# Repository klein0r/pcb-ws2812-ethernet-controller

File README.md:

# WS2812 / SK6812 Ethernet Controller Custom PCB

Control your addressable LED with custom software like [WLED](https://github.com/Aircoookie/WLED)

[Gerber-Files](https://github.com/klein0r/pcb-ws2812-ethernet-controller/releases)

## Important notes

The [WT32-ETH01](https://en.wireless-tag.com/product-item-2.html) has been released in different revisions. This adapter has been tested with revision 1.2 (length of the WT32-ETH01 PCB is ~5.5 cm).

**Some revisions may not fit!** I've received a photo of revision 1.4 with a PCB length of ~6.0 cm. Use PCB version 2.0 (or later) of this project to ensure the adapter will fit.

## Preview

## Components

- U1: WT32-ETH01 ESP32
- U2: SN74AHCT125DR
- C1: Capacitor Radial 3.8mm 1000μF 6.3V
- F1: Stelvio Kontek STV PTF/75 + Fuse 5x20mm, 5A (max. 6A)
- J1: Barrel Jack Connector - Wuerth 6941xx301002
- J2: PHC 1725669 - MPT 0,5 / 3-2,54
- J3: PHC 1725669 - MPT 0,5 / 3-2,54
- J4: 1x4 2.54mm Male Pin Headers (for flashing - soldering not required)
- J5: 1x2 2.54mm Male Pin Headers (for flashing - soldering not required / jumper)
- R1: Resistor 0805 330
- R2: Resistor 0805 330

[Component list (Affiliate-Link)](https://haus-auto.com/p/rei/ListeWS2812Eth)

## GPIO

- GPIO2 = Data line 1 of addressable strip
- GPIO4 = Data line 2 of addressable strip

## License

The MIT License (MIT)

Copyright (c) 2026 Matthias Kleine <info@haus-automatisierung.com>

Permission is hereby granted, free of charge, to any person obtaining a copy
of this software and associated documentation files (the "Software"), to deal
in the Software without restriction, including without limitation the rights
to use, copy, modify, merge, publish, distribute, sublicense, and/or sell
copies of the Software, and to permit persons to whom the Software is
furnished to do so, subject to the following conditions:

The above copyright notice and this permission notice shall be included in
all copies or substantial portions of the Software.

THE SOFTWARE IS PROVIDED "AS IS", WITHOUT WARRANTY OF ANY KIND, EXPRESS OR
IMPLIED, INCLUDING BUT NOT LIMITED TO THE WARRANTIES OF MERCHANTABILITY,
FITNESS FOR A PARTICULAR PURPOSE AND NONINFRINGEMENT. IN NO EVENT SHALL THE
AUTHORS OR COPYRIGHT HOLDERS BE LIABLE FOR ANY CLAIM, DAMAGES OR OTHER
LIABILITY, WHETHER IN AN ACTION OF CONTRACT, TORT OR OTHERWISE, ARISING FROM,
OUT OF OR IN CONNECTION WITH THE SOFTWARE OR THE USE OR OTHER DEALINGS IN
THE SOFTWARE.

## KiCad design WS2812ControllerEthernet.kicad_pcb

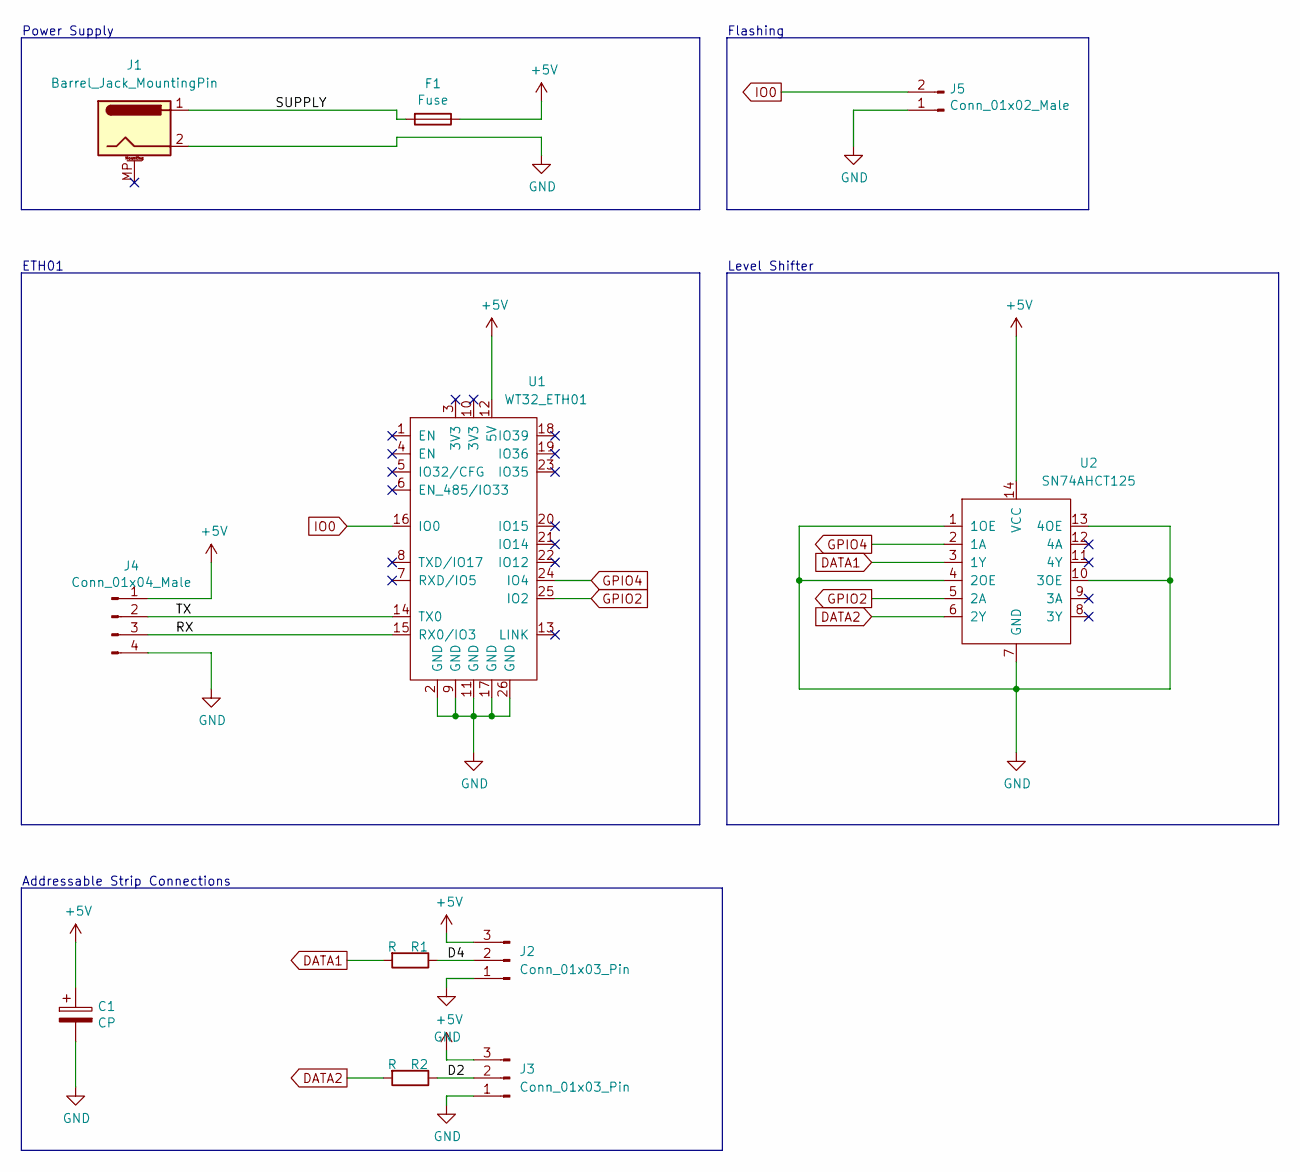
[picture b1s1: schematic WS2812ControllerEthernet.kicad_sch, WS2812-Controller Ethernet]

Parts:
C1: CP; CP_Radial_D8.0mm_P3.80mm
F1: Fuse; Fuse-PTF75_Stelvio
J1: Barrel_Jack_MountingPin; BarrelJack_Wuerth_6941xx301002
J2, J3: Conn_01x03_Pin; TerminalBlock_Phoenix_MPT-0,5-3-2.54_1x03_P2.54mm_Horizontal
J4: Conn_01x04_Male; PinHeader_1x04_P2.54mm_Vertical
J5: Conn_01x02_Male; PinHeader_1x02_P2.54mm_Vertical
R1, R2: R; R_0805_2012Metric_Pad1.20x1.40mm_HandSolder
U1: WT32_ETH01; WT32_ETH01_long
U2: SN74AHCT125; SN74AHCT125D

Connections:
+5V: C1.1, F1.1, J2.3, J3.3, J4.1, U1.12 (5V), U2.14 (VCC)
/D2: J3.2, R2.1
/D4: J2.2, R1.1
/RX: J4.3, U1.15 (RX0/IO3)
/SUPPLY: F1.2, J1.1
/TX: J4.2, U1.14 (TX0)
DATA1: R1.2, U2.3 (1Y)
DATA2: R2.2, U2.6 (2Y)
GND: C1.2, J1.2, J2.1, J3.1, J4.4, J5.1, U1.2 (GND), U1.9 (GND), U1.11 (GND), U1.17 (GND), U1.26 (GND), U2.1 (1OE), U2.4 (2OE), U2.7 (GND), U2.10 (3OE), U2.13 (4OE)
GPIO2: U1.25 (IO2), U2.5 (2A)
GPIO4: U1.24 (IO4), U2.2 (1A)
IO0: J5.2, U1.16 (IO0)

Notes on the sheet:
Addressable Strip Connections
Power Supply
ETH01
Flashing
Level Shifter

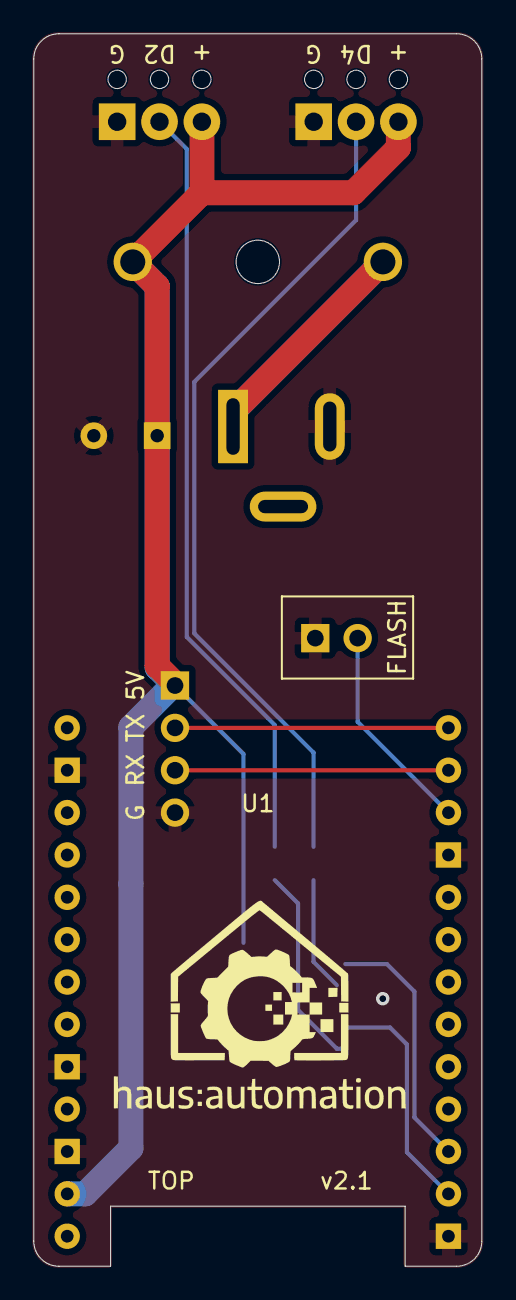
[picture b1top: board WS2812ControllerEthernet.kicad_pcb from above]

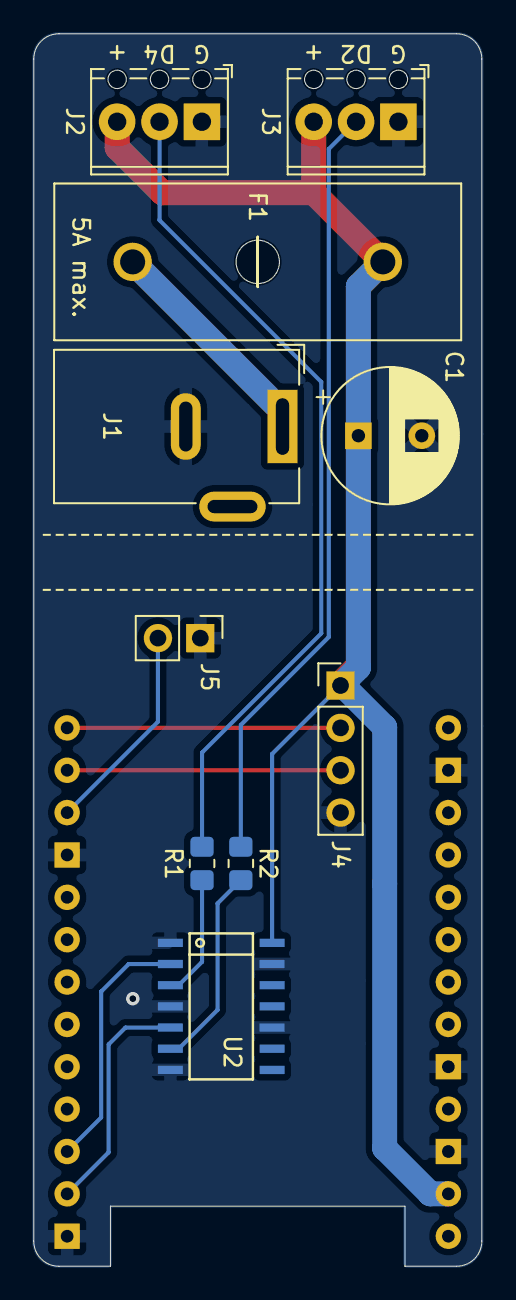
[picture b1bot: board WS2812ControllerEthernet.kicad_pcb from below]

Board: 2 copper layers, 26.9 x 73.9 mm, 11 parts (10 on the bottom side), 12 nets.

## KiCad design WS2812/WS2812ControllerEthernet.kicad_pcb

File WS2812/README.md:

# WS2812 / SK6812 Ethernet Controller Custom PCB

Control your addressable LED with custom software like [WLED](https://github.com/Aircoookie/WLED)

[Gerber-Files](https://github.com/klein0r/pcb-ws2812-ethernet-controller/releases)

## Preview

## Components

- WT32-ETH01 ESP32
- C1: Capacitor Radial 3.8mm 1000μF 6.3
- F1: Stelvio Kontek STV PTF/75 + Fuse 5x20mm, 5A (max. 6A)
- J1: PHC 1725672 - MPT 0,5 / 4-2,54
- J2: PHC 1725669 - MPT 0,5 / 3-2,54
- J3: 1x4 2.54mm Male Pin Headers (for flashing - soldering not required)
- J4: 1x2 2.54mm Male Pin Headers (for flashing - jumper)
- U1: WT32-ETH01
- U2: SN74AHCT125DR
- R1: Resistor 0805 330

[Component list (Affiliate-Link)](https://haus-auto.com/p/rei/ListeWS2812Eth)

## GPIO

- GPIO2 = Data line of addressable strip

## License

The MIT License (MIT)

Copyright (c) 2022 Matthias Kleine <info@haus-automatisierung.com>

Permission is hereby granted, free of charge, to any person obtaining a copy
of this software and associated documentation files (the "Software"), to deal
in the Software without restriction, including without limitation the rights
to use, copy, modify, merge, publish, distribute, sublicense, and/or sell
copies of the Software, and to permit persons to whom the Software is
furnished to do so, subject to the following conditions:

The above copyright notice and this permission notice shall be included in
all copies or substantial portions of the Software.

THE SOFTWARE IS PROVIDED "AS IS", WITHOUT WARRANTY OF ANY KIND, EXPRESS OR
IMPLIED, INCLUDING BUT NOT LIMITED TO THE WARRANTIES OF MERCHANTABILITY,
FITNESS FOR A PARTICULAR PURPOSE AND NONINFRINGEMENT. IN NO EVENT SHALL THE
AUTHORS OR COPYRIGHT HOLDERS BE LIABLE FOR ANY CLAIM, DAMAGES OR OTHER
LIABILITY, WHETHER IN AN ACTION OF CONTRACT, TORT OR OTHERWISE, ARISING FROM,
OUT OF OR IN CONNECTION WITH THE SOFTWARE OR THE USE OR OTHER DEALINGS IN
THE SOFTWARE.

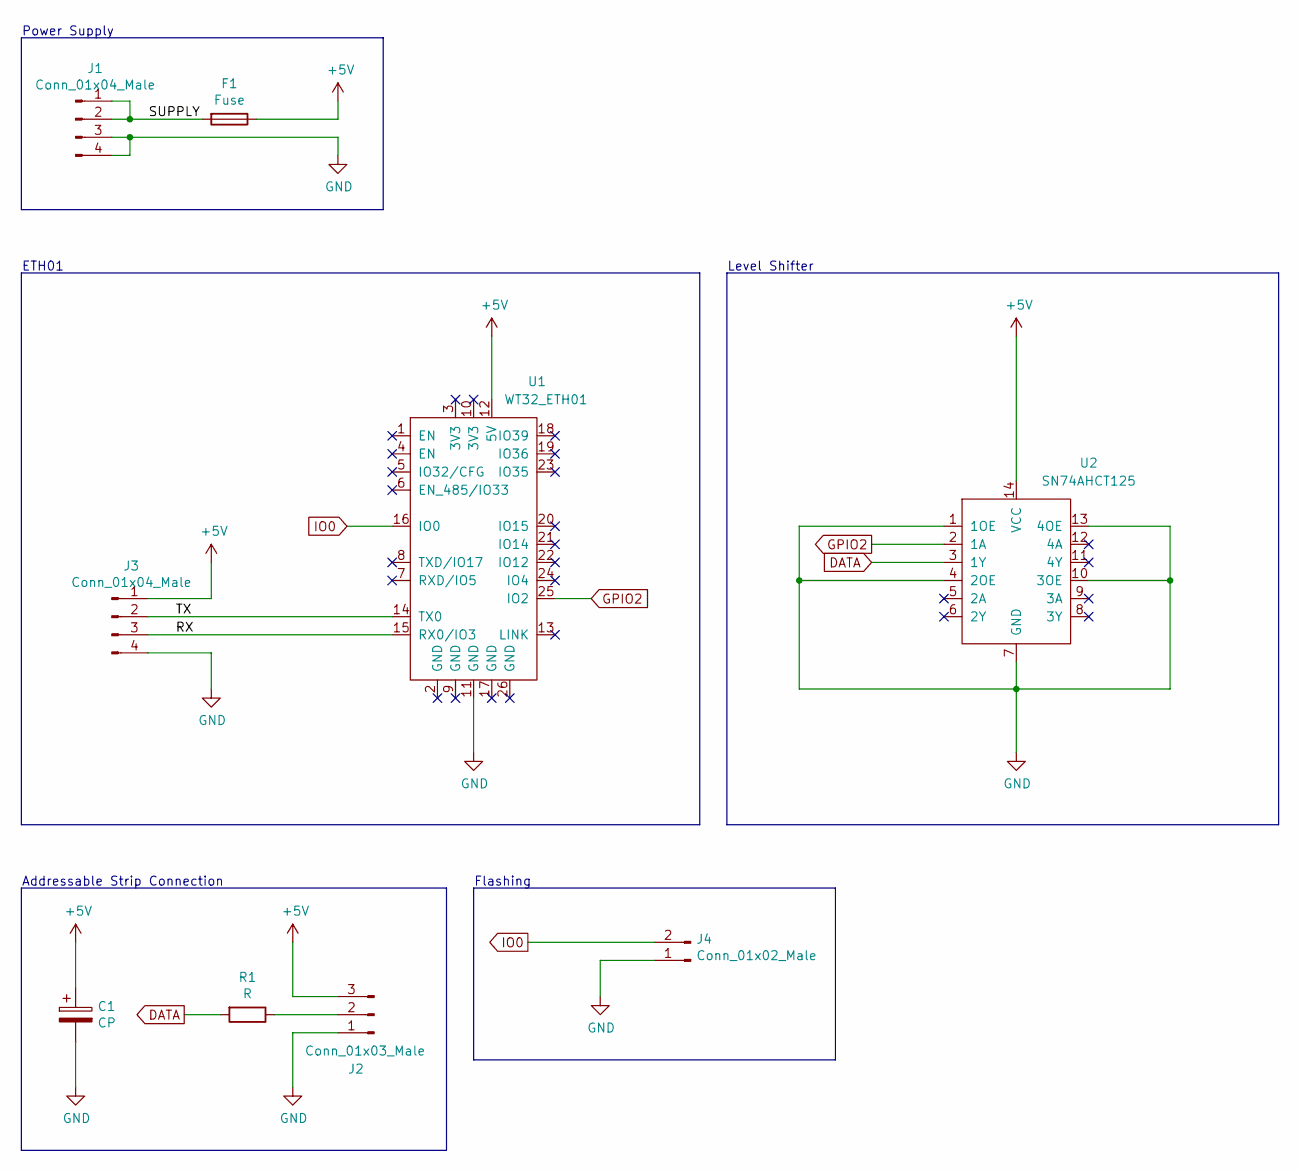
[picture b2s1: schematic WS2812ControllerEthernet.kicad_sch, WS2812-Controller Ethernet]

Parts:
C1: CP; CP_Radial_D8.0mm_P3.80mm
F1: Fuse; Fuse-PTF75_Stelvio
J1: Conn_01x04_Male; TerminalBlock_Phoenix_MPT-0,5-4-2.54_1x04_P2.54mm_Horizontal
J2: Conn_01x03_Male; TerminalBlock_Phoenix_MPT-0,5-3-2.54_1x03_P2.54mm_Horizontal
J3: Conn_01x04_Male; PinHeader_1x04_P2.54mm_Vertical
J4: Conn_01x02_Male; PinHeader_1x02_P2.54mm_Vertical
R1: R; R_0805_2012Metric_Pad1.20x1.40mm_HandSolder
U1: WT32_ETH01
U2: SN74AHCT125; SN74AHCT125D

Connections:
+5V: C1.1, F1.1, J2.3, J3.1, U1.12 (5V), U2.14 (VCC)
/RX: J3.3, U1.15 (RX0/IO3)
/SUPPLY: F1.2, J1.1, J1.2
/TX: J3.2, U1.14 (TX0)
DATA: R1.2, U2.3 (1Y)
GND: C1.2, J1.3, J1.4, J2.1, J3.4, J4.1, U1.11 (GND), U2.1 (1OE), U2.4 (2OE), U2.7 (GND), U2.10 (3OE), U2.13 (4OE)
GPIO2: U1.25 (IO2), U2.2 (1A)
IO0: J4.2, U1.16 (IO0)
unnamed: J2.2, R1.1

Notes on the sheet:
Addressable Strip Connection
Power Supply
ETH01
Flashing
Level Shifter

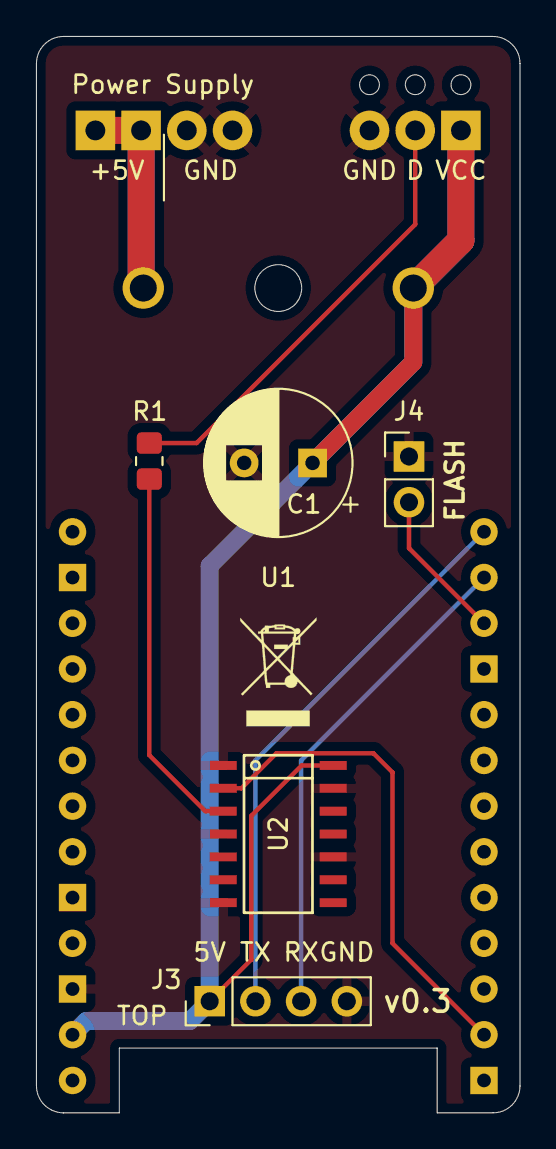
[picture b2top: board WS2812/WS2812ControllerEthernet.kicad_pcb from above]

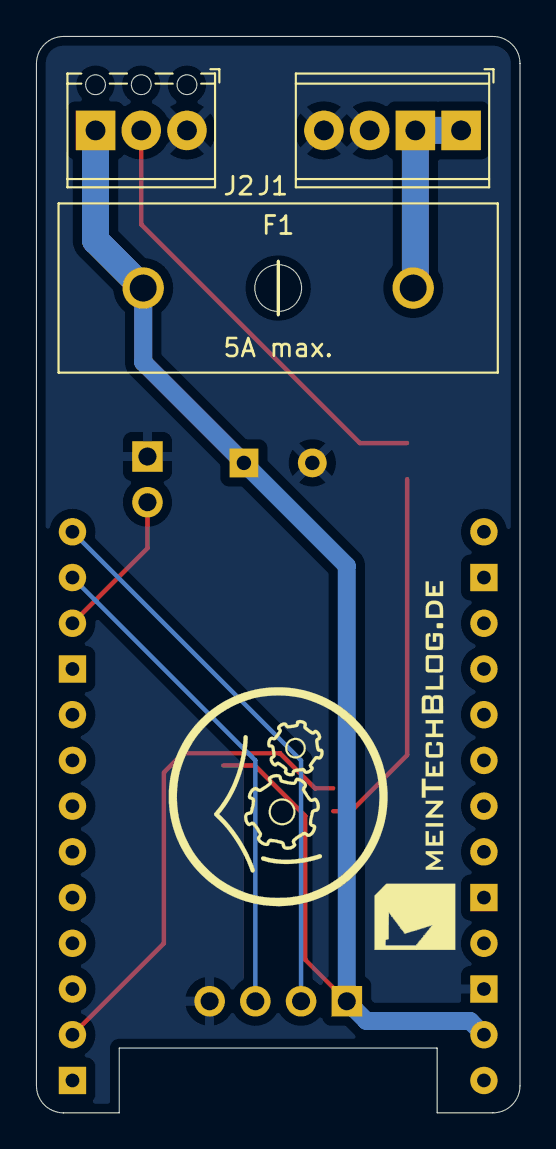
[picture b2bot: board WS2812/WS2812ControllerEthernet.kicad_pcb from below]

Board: 2 copper layers, 26.9 x 59.8 mm, 9 parts (3 on the bottom side), 9 nets.

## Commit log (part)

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2021-05-12 Work in Progress
2021-05-13 First release, ready to order
2021-06-10 Fixed wrong label
2021-06-10 Updated preview
2021-06-13 v0.2
2021-09-30 Added level shifter
2021-10-13 Preview Photo
2022-01-30 Update LICENSE
2022-01-30 Updated to KiCad 6
2022-05-02 draft for APA102
2023-08-03 Updated layout
2023-08-15 Updated preview images
2024-02-19 Added additional GPIO for strip
2024-05-07 KiCad 8
2024-05-17 v1.0
2024-05-24 v1.1
2024-05-24 Component list
2024-08-23 v2.0
2025-08-14 KiCad 9
2026-01-28 Year 2026
    Updated copyright year in the LICENSE file.
2026-01-28 Year 2026
